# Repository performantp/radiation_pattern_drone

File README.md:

# Radiation Pattern Drone Project 
README

Die mit MMANA oder 4NEC berechneten Antennen sollen mit einer Drohne auf Abstrahlungscharakteristik und Abstrahlungswinkel ausgemessen und überprüft werden. Die erstellten versionierten Dateien sollen für weitere Projektmitglieder lesbar abgelegt werden.

Release 1.3a (diese Aufgabe wurde im September 2021 unterbrochen, weitere Hinweise und Details sind am Schluss aufgeführt).

Release 1.4a es wurden anschliessend zwei Lösungsvarianten evaluiert. 

Variante 1: Welche anfangs Oktober 2021 nun bereits mit einem ersten Test läuft, ist folgende: Mit einem Raspi auf dem rtl_power läuft und RTL-SDR mit einen Transverter
(47g) wird ein Frequenzbereich von 7-14 MHz überwacht und die gemessenen Werte werden mit einem Python Programm auf einem Raspi Zero W (40g) abgegriffen und dargestellt (Kabel und Antennen ca. 50g). Die ersten Messergebnisse sind so, dass man die gemessenen Werte noch gegenüber dem S-Level kalibrieren muss.

Hier ein Test, welcher Signale mit verschiedenen Stärken aufzeigt. Es gibt im Moment jeweils pro Messung ein Bild und eine CSV-Datei. 

Variante 2: Im Hintergrund ist noch folgende zweite Lösung angedacht und die entsprechende Hardware wurde im September 2021 bereits beschafft.
Mit einem Raspi Zero W (40g) sollen die Messwerte von einem RTL-SDR mit integriertem Transverter aufgesammelt werden und die Daten anschliessend mit rtl_power und/oder Python ausgewertet werden.
Es gibt nun ein paar Fotos dazu. Hier ein Rasperi Zero W ohne Gehäuse. 

Das ist ein ganz leichter Rasperi pi-pico mit nur 4g und kann Interpreter-mässig das gleiche wie ein Rasperi Zero W. 

Das ist ein Rasperi Zero W, welcher in einem Gehäude ist und u.U. auch je nach Ausbau noch einen Ventilator hat. 

Der Transverter vor dem RTL. 

Hier sieht man alle Teile vom Transverter, über RTL-SDR und Rasperi im Testaufbau auf dem Balkon von Daniel HB9GVD. Daran angeschlossen ist natürlich noch eine Antenne (nicht sichtbar). 

Wo wir dieses Teil einsetzen hat Martin HB9GYF nach einer Woche vergessen, aber das Bild wird eingetragen und dann nochmals nachgefragt. 

Zu der Programmiersprache Python wurde von HB9FRV Ende September 2021 ein USKA HamAcademy durchgeführt. Es gibt voraussichtlich noch weitere Python Kurse. Auch wie man mit Python SDR Implementationen erstellt, wird von Mathias HB9FRV im Rahmen der USKA HamAcademy vermittelt. Daniel HB9GVD wird am 23.10.2021 am Kurs teilnehmen. Die Kurse sind für USKA Mitglieder mit 60.- CHF Kursgeld zugänglich. Auch dieser Kurs wird ev. wiederholt.

Python ist eine Interpreter Sprache, aber die Source wird auf eine andere Plattform mitgeben. Es wird dann zuerst (einmalig) eine Art Compiler gestartet, der einmal abläuft und dann startet der Interpreter auf diesem Element auf. 

Das Team sucht weitere Interessierte, wenn möglich mit Python Kompetenz, welche die Python Aktivitäten unterstützen können. Interessenten melden sich bitte bei Martin HB9GYF oder Daniel HB9GVD. Martin HB9GYF hat sich Ende Oktober 2021 in der Rolle als Project Manager für den zweiten Python Kurs in der HamAcademy im November 2021 eingetragen, ist aber auf der Warteliste gelandet. Was ist das Ziel? Verstehen, ob ein Project Manager den Python Source Code auf den Ablauf eines Python Programm "lesen" kann. 

Release 1.4b (nächste Aufgabe)
Mit einer grösseren Drohne und einer Last von ca. 150g und einem Gesamtgewicht von mehr als 1kg eine zu messenden Antenne (voraussichtlich eine Small Transmitting Loop (STL)) in einem Stufenflug zu erfliegen, damit daraus die Abstrahlcharakteristik der Antenne ermittelt werden kann. Analysieren wieviele Messungen im Flug pro Sekunde durchgeführt werden müssen, damit die Abstrahlcharakteristik ermittelt werden kann. Analysieren, ob sich im PoC dazu der WSPR-Ansatz eignet. Analysieren, wie z.B. grosse Beam-Antennen auf so kleine Aussendungen in 200m rund um die Antenne reagieren/gemessen werden können. Analysieren, ob sich die kleine Stabantenne im PoC eignet oder ob eine Drahtantenne realisiert werden soll. Analysieren, wie sich eine Aussendung z.B. mit 1W im Flug eignet. Die generelle Datensammlung soll im PoC überprüft werden. Die Datenauswertung im PoC soll nach einem Flug innert 12h vorliegen.

Eine Drohne herzustellen inkl. Akku, GPS und allem SDR-Equipmnet unter 250g wäre interessant, um unter den (künftigen) restriktiven gesetzlichen Anforderungen "in die Luft" zu kommen.

Die Drohne Plan B1 kann mehrere Way Points xyz fliegen und so müssten wir in der Lage sein, unser Stufenprofil auf verschiedenen Höhen auszufliegen. Die Drohne Plan B2 wurde bestellt und ist im September 2021 ebenfalls in der Schweiz bei Daniel HB9GVD. 

Release 1.4c (übernächste Aufgabe)
beinhaltet die Realisierung des sogenannten Datensammelpunkts gemäss Datenmodell sowie der Speicherung der Daten für spätere Auswertungen. Die Empfangssignalstärke sowie die GPS-Daten (es könnten die GPS-Daten der Drohne sein) sollen aufgenommen, zeitlich verknüpft und raw gespeichert werden. 

Release 1.5 (weitere Aufgaben) 
beinhaltet die Realisierung von Auswertungen nach Abzug über WLAN oder Bluetooth von der Drohne auf einen PC. Diese können als erstes Proof of Concept für die Auswertung des Abstrahlwinkels und den weiteren Sendekeulen manuell oder automatisch mit einer Python Programmierung erfolgen. 

---------------------------------------------------------------------------------------------------------------------------------------------------------------------------------
Release 1.3a (diese Aufgabe wurde im September 2021 unterbochen)

Aufgabenstellung: Beinhaltet die Realisierung auf einem eigenen Board mit einem ESP32 Prozessor für die Scriptsprache Phyton mit WLAN und Bluetooth Schnittstelle, welches mit KICAD geplant wird (Design per 15.04.2021 abgeschlossen) und dessen PCB-Fertigung in China inklusive Bestückung erfolgt. Dabei können nur Bauteile vom Produzenten auf der Platine eingebaut werden. Die Integration des Silicon Labs SDR Chipset SI4734-D60-GU (SSOP Bauweise) und weitere 1-2 Bauteile werden dann abschliessend manuell in der Schweiz bestückt und danach getestet. Die Box ohne Antenne ist ca. 5x5x3 cm gross und wird mit ca. 30g Last berechnet. Professionelle Drohne aus US mit 780g Fluggewicht und Funktionen wie u.a. Motion Tracking, Way Point Skills ist nach längeren Shiping Aktionen in der CH eingetroffen und sie wurde getestet. Die vorhandenen Flug Management Skills sind hervorragend, aber u.a. aus Lizenzgründen vermutlich "zu gut". Aus der Sicht maximales Gesamtgewicht, welches unter 250g angestrebt wird (somit ist ein Flug bis 250m Höhe ohne Voranmeldung möglich, gesetzliche Randbedingung) wurde für das PoC eine noch leichtere Drohne bestellt. Die PoC Anforderungen an diese leichte Drohne sind mit Last gesamthaft nicht schwerer als 250g, Way Points zu fliegen, Position halten zu können und alles bis ca. 15 km Wind auf +/- 0.5m genau zu fliegen, und dabei die GPS-Daten zu speichern.  

Das SDR PCB ist am 08.05.2021 fertig "designed" und geht bald in die Fertigung nach China. Screenshot von Daniel HB9GVD erhalten. 

Warum wurde unterbrochen? Beim Testen des Boards sind im August/September 2021 Design-Fehler aufgetreten. Einige Verbindungen konnten zwar mit einer ad hoc Verbindung/Korrektur korrigiert werden. Trotz mehreren Anläufen das Board "zum Laufen" zu bringen, und weiteren Arbeiten wurde der "Durchbruch" leider nicht erreicht. Die Arbeiten zu Release 1.3a wurden deshalb vorläuftig eingestellt, alternative Lösungswege wurden analysiert und gefunden. Gerne lädt das Team Interessierte ein, das Board und die entsprechende Programmierung weiterzuführen. Daniel HB9GVD teilt sein Wissen gerne. Die Gewichtsvorteile der eigenen Hardware würden eher eine <250g Drohne erlauben.

--------------------------------------------------------------------------------------------------------------------------------------------------------------------------------
Abgeschlossene oder gestrichene Releases:
Release 1.1 (am 23.12.2020 abgeschlossen)
beinhaltete die Realisierung im November/Dezember 2020 auf einem Breadboard mit dem Silicon Labs Chipset 30, welcher "nur" MW und FM kann. Die Realiserung mit dem Display ST7735SB mit einer SD-Speicherkarte wurde am 01.12.2020 wegen Inkompatibilität zur Original Display Library eingestellt. Weiter verfolgt wurde die Realisierung mit dem Display ST7735S. Die Realisierung wurde in Woche 50/2020 erfolgreich abgeschlossen. Die erreichten Ergebnisse von diesem Release sind in der Dokumentation festgehalten. 

Release 1.2 (auf diesen Schritt wird am 23.12.2020 verzichtet, weil zwei andere OM's diesen Nachweis bereits vollbracht haben, Verweis auf zwei you tube Videos)
beinhaltet die Realisierung auf einem Breadboard mit dem Silicon Labs SDR Chipset SI4734-D60-GU (in der SSOP Bauweise mit oder ohne Breakout Board), welcher MW, FM und SW, inbesondere LSB, USB und CW, kann. Das Display und die Bedienung wird mit einer App realisiert. 

--------------------------------------------------------------------------------------------------------------------------------------------------------------------------------

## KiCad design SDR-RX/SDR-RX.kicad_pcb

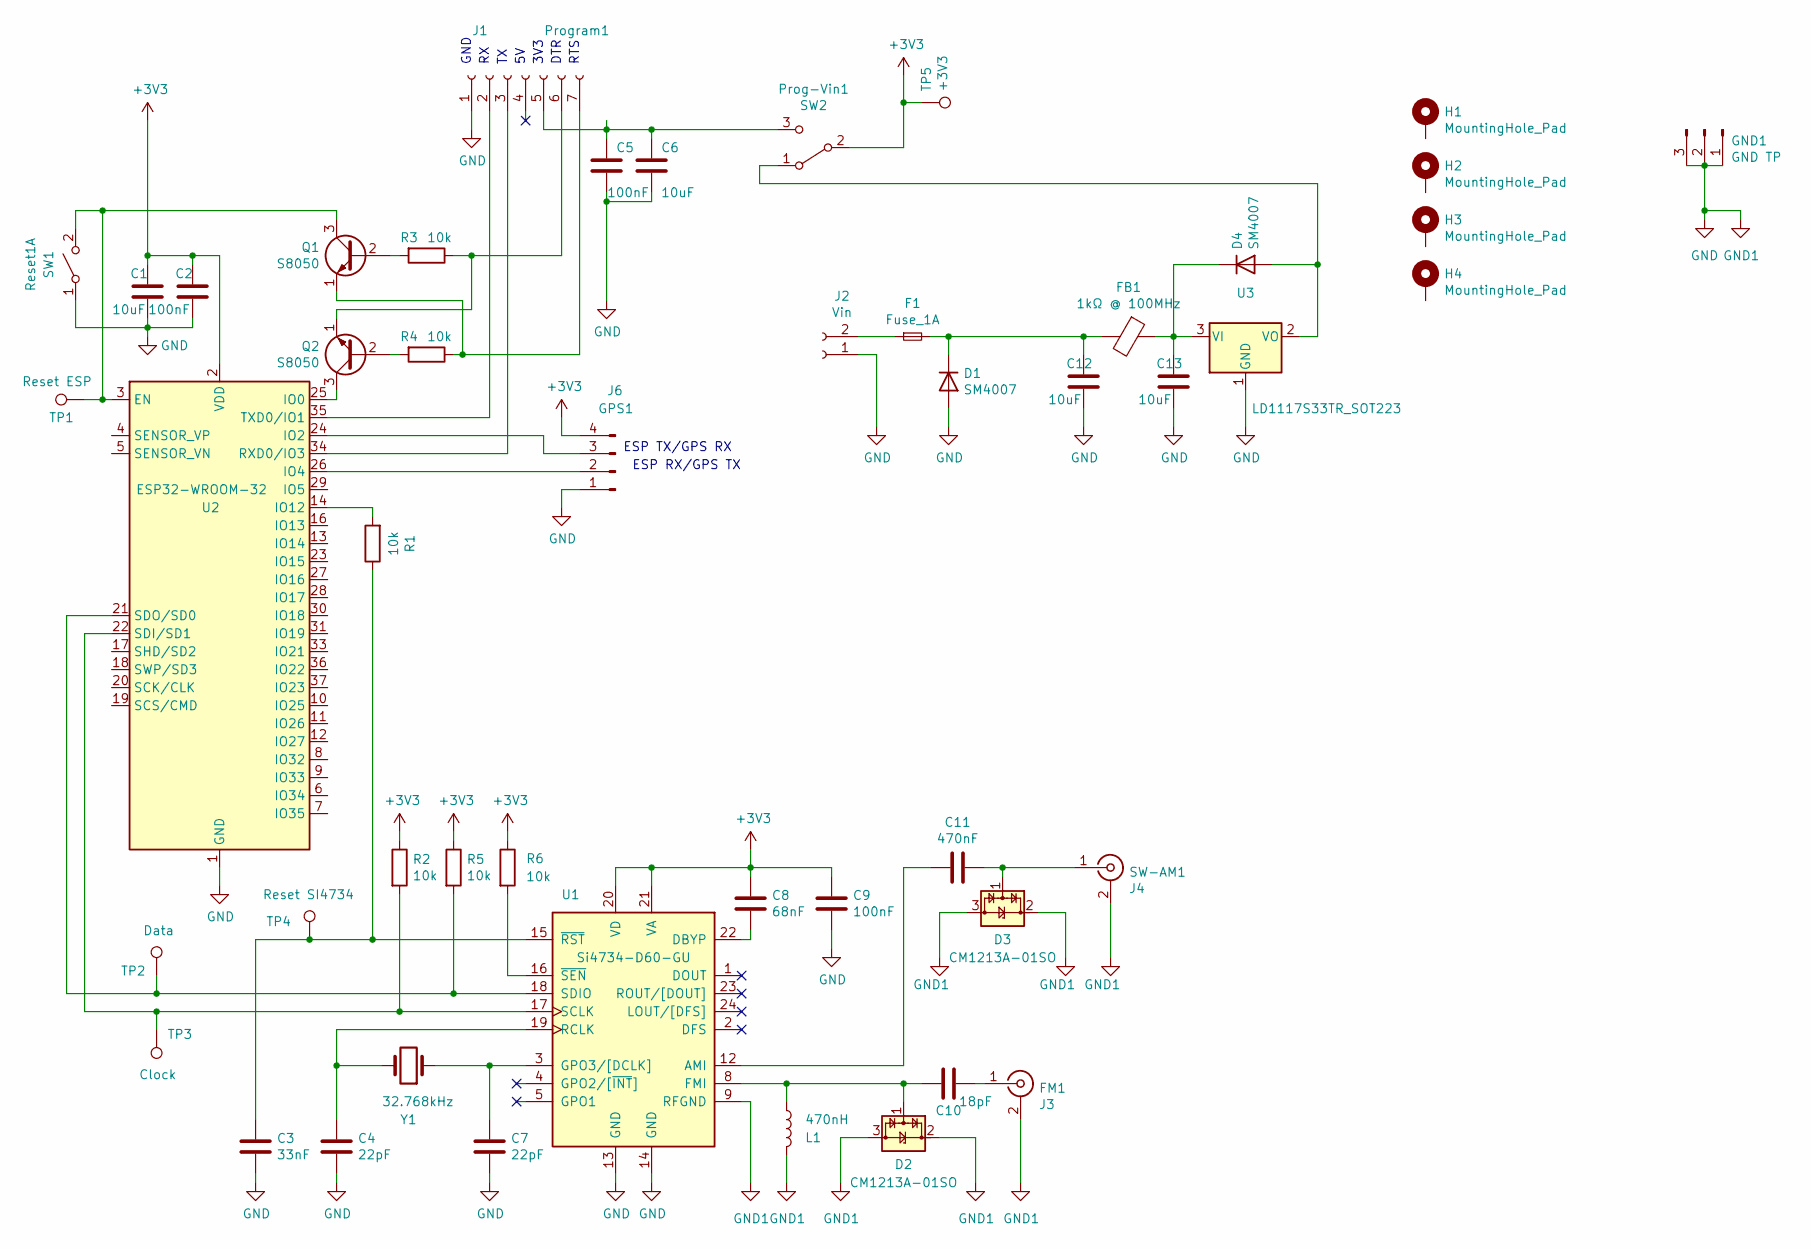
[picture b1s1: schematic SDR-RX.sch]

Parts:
C1, C6, C12, C13: 10uF; C_1206_3216Metric_Pad1.33x1.80mm_HandSolder; LCSC Part # C13585
C2, C5, C9: 100nF; C_0603_1608Metric_Pad1.08x0.95mm_HandSolder; LCSC Part # C14663
C3: 33nF; C_0603_1608Metric_Pad1.08x0.95mm_HandSolder; LCSC Part # C21117
C4, C7: 22pF; C_0603_1608Metric_Pad1.08x0.95mm_HandSolder; LCSC Part # C1653
C8: 68nF; C_0603_1608Metric_Pad1.08x0.95mm_HandSolder; LCSC Part # C31658
C10: 18pF; C_0603_1608Metric_Pad1.08x0.95mm_HandSolder; LCSC Part # C1647
C11: 470nF; C_0603_1608Metric_Pad1.08x0.95mm_HandSolder; LCSC Part # C1623
D1, D4: SM4007; D_1206_3216Metric_Pad1.42x1.75mm_HandSolder; LCSC Part # C64898
D2, D3: CM1213A-01SO; SOT-23
F1: Fuse_1A; Fuse_1206_3216Metric_Pad1.42x1.75mm_HandSolder; LCSC Part # C182308
FB1: 1kΩ @ 100MHz; L_1210_3225Metric_Pad1.42x2.65mm_HandSolder; LCSC Part # C124093
FM1: J3; SMA_Samtec_SMA-J-P-X-ST-EM1_EdgeMount
GND1: GND TP; PinHeader_1x03_P2.54mm_Vertical
GPS1: J6; JST_SH_BM04B-SRSS-TB_1x04-1MP_P1.00mm_Vertical-GPS; LCSC Part # C239522
H1, H2, H3, H4: MountingHole_Pad; MountingHole_2.7mm_Pad_Via
J2: Vin; JST_XH_B2B-XH-A_1x02_P2.50mm_Vertical
L1: 470nH; L_0603_1608Metric_Pad1.05x0.95mm_HandSolder; LCSC Part # C1034
Prog-Vin1: SW2; SW_SPDT_CK-JS102011SAQN; LCSC Part # C160876
Program1: J1; JST_XH_S7B-XH-A-1_1x07_P2.50mm_Horizontal
Q1, Q2: S8050; SOT-23_Handsoldering; LCSC Part # C2146
R1, R2, R3, R4, R5, R6: 10k; R_0603_1608Metric_Pad0.98x0.95mm_HandSolder; LCSC Part # C25804
Reset1: SW1; SW_SPST_B3SL-1002P; LCSC Part # C318887
SW-AM1: J4; SMB_Jack_Vertical
TP1: Reset ESP; TestPoint_Pad_D1.5mm
TP2: Data; TestPoint_Pad_D1.5mm
TP3: Clock; TestPoint_Pad_D1.5mm
TP4: Reset SI4734; TestPoint_Pad_D1.5mm
TP5: +3V3; TestPoint_Pad_D1.5mm
U1: Si4734-D60-GU; SSOP-24_3.9x8.7mm_P0.635mm
U2: ESP32-WROOM-32; LCSC Part # C82899
U3: LD1117S33TR_SOT223; SOT-223-3_TabPin2; LCSC Part # C23984
Y1: 32.768kHz; Crystal_SMD_3215-2Pin_3.2x1.5mm; LCSC Part # C32346

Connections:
+3V3: C1.1, C2.1, C8.1, C9.1, GPS1.4, Prog-Vin1.2 (B), R2.1, R5.1, R6.1, TP5.1, U1.20 (VD), U1.21 (VA), U2.2 (VDD)
GND: C1.2, C2.2, C3.2, C4.1, C5.2, C6.2, C7.2, C9.2, C12.2, C13.2, D1.2 (A), D2.2 (VP), D2.3 (VN), D3.2 (VP), D3.3 (VN), FM1.2 (Ext), GND1.1, GND1.2, GND1.3, GPS1.1, GPS1.MP, J2.1, L1.2, Program1.1, Reset1.1 (A), SW-AM1.2 (Ext), U1.9 (RFGND), U1.13 (GND), U1.14 (GND), U2.1 (GND), U2.15 (GND), U2.38 (GND), U2.39 (GND), U3.1 (GND)
unnamed: C3.1, R1.1, TP4.1, U1.15 (~RST)
unnamed: C4.2, U1.19 (RCLK), Y1.2
unnamed: C5.1, C6.1, Prog-Vin1.3 (C), Program1.5
unnamed: C7.1, U1.3 (GPO3/[DCLK]), Y1.1
unnamed: C8.2, U1.22 (DBYP)
unnamed: C10.1, FM1.1 (In)
unnamed: C10.2, D2.1 (CH1), L1.1, U1.8 (FMI)
unnamed: C11.1, D3.1 (CH1), SW-AM1.1 (In)
unnamed: C11.2, U1.12 (AMI)
unnamed: C12.1, D1.1 (K), F1.2, FB1.2
unnamed: C13.1, D4.1 (K), FB1.1, U3.3 (VI)
unnamed: D4.2 (A), Prog-Vin1.1 (A), U3.2 (VO)
unnamed: F1.1, J2.2
unnamed: GPS1.2, U2.26 (IO4)
unnamed: GPS1.3, U2.24 (IO2)
unnamed: Program1.2, U2.35 (TXD0/IO1)
unnamed: Program1.3, U2.34 (RXD0/IO3)
unnamed: Program1.6, Q2.1 (E), R3.1
unnamed: Program1.7, Q1.1 (E), R4.1
unnamed: Q1.2 (B), R3.2
unnamed: Q1.3 (C), Reset1.2 (B), TP1.1, U2.3 (EN)
unnamed: Q2.2 (B), R4.2
unnamed: Q2.3 (C), U2.25 (IO0)
unnamed: R1.2, U2.14 (IO12)
unnamed: R2.2, TP3.1, U1.17 (SCLK), U2.22 (SDI/SD1)
unnamed: R5.2, TP2.1, U1.18 (SDIO), U2.21 (SDO/SD0)
unnamed: R6.2, U1.16 (~SEN)

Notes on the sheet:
3V3
DTR
RTS
GND
ESP RX/GPS TX
ESP TX/GPS RX

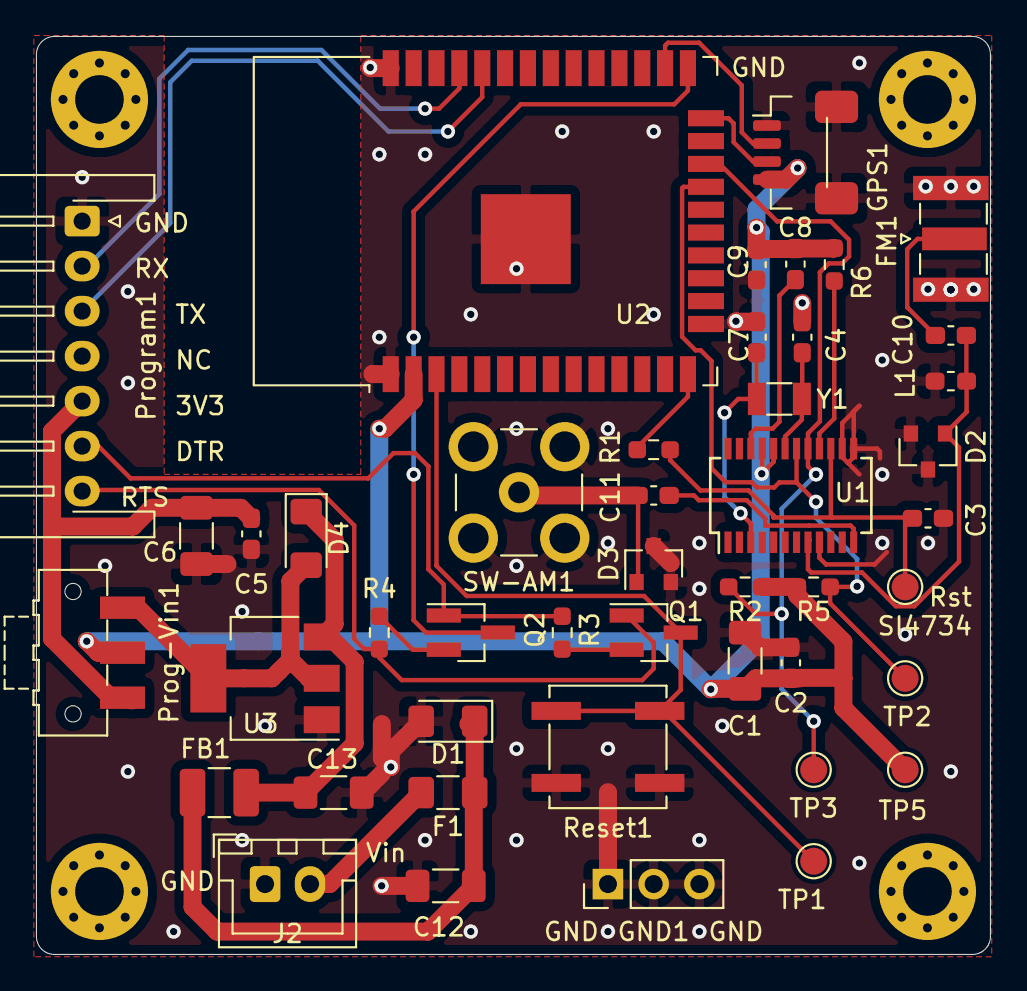
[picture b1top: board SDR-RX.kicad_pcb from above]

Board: 2 copper layers, 53.0 x 51.0 mm, 49 parts (0 on the bottom side), 29 nets.

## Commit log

2020-12-02 Create README.md
    Release Planung am 02.12.2020 erstellt.
    Im Moment arbeiten wir für den Release 1.1 im Main und wir werden am Schluss den Release schliessen, wenn die Arbeiten für Release 1.2 beginnen.
2020-12-02 Update README.md
    Typos korrigiert.
2020-12-02 Update README.md
    Noch zwei Typos gefunden und korrigiert.
2020-12-02 Add files via upload
    Diese vier Dateien sind von Martin mit dem Stand vom 01.12.2020. Es gibt in der Zwischenzeit betreits schon neuere Arbeitsdokumente, und auch dieser Update wird so dann noch ausgetestet.
2020-12-02 Add files via upload
    Dies ist die Spezifikation vom Hersteller Silicon Labs über die leicht neuere SDR Chipreihe mit zwei unterschiedlichen Bauformen. Dabei ist darauf zu achten, dass wir erstens jeweils die Funktion SW 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
2020-12-02 Add files via upload
    Der Hersteller Silicon Labs gibt Unterlagen und Spezifikationen für die Antenne bekannt, welche berücksichtigt werden müssen.
2020-12-02 Add files via upload
    Die ist ein Schema, welches das Projekt von Xhackster verwendet. In diesem Fall wird der Chipset SI4630-D60 in der quadratischen Form verwendet, welcher aber bereits SW kann. Diesen Chip haben wir fü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
2020-12-02 Add files via upload
    Dies ist der Original Code aus dem Xhackster Projekt, welches mit dem SI4730-D60 Chip (mit SW) arbeitet. Wir haben diesen Code mit den entsprechenden Libraries ausprobiert, aber am 03.12.2020 noch ni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
2020-12-03 Update README.md
    Mit dem Release 1.2a "Empfangssignalstärke verknüpft mit den GPS-Daten am Datensammlungspunkt " werden wir überprüfen können, wie der Empfang an einer Live-Antenne im Feld aufgenommen werden können.
2020-12-04 Changed main title in README file
2020-12-04 Originalcode von CesarSound (hackster.io)
    Dieser Commit enthält den von CesarSound auf hackster.io publizierten Originalcode zur Ansteuerung des si4730/35 Chips inkl. TFT Display. Sein Schema sowie die notwendigen Arduino-Library Abhängigkei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
2020-12-04 Source Code und Schema von CesarSound aus Wurzelverzeichnis gelöscht
    Diese DAten sind neu im RX_SI4735_30_TFT_ST7735_SHARE_JCR_REV_2_1 Unterverzeichnis zu finden.
2020-12-04 Verschiebe si4730 Datenblatt ins *datasheets" Unterverzeichnis.
2020-12-05 Update README.md
    Die Bezeichnung SI4734-D60-GU an zwei Stellen korrigiert.
2020-12-06 Update README.md
    SI4734-D60-GU korrekt eingetragen
2020-12-06 Delete Anforderungskatalog Mit einer Drohne eine Antenne ausmessen.docx
    Martin löscht diese Datei, weil ich sie in dem Ordner Docs und nicht flat haben will. Aber mit GitHub Desktop habe ich das 'rename' wie es Mathias in Tortoise gezeigt hat, nicht verstanden.
2020-12-06 Delete Anforderungskatalog Mit einer Drohne eine Antenne ausmessen.html
    Martin löscht diese Datei, weil ich sie in dem Ordner Docs und nicht flat haben will. Aber mit GitHub Desktop habe ich das 'rename' wie es Mathias in Tortoise gezeigt hat, nicht verstanden.
2020-12-06 Delete Anforderungskatalog Mit einer Drohne eine Antenne ausmessen.mmap
    Martin löscht diese Datei, weil ich sie in dem Ordner Docs und nicht flat haben will. Aber mit GitHub Desktop habe ich das 'rename' wie es Mathias in Tortoise gezeigt hat, nicht verstanden.
2020-12-06 Delete Anforderungskatalog Mit einer Drohne eine Antenne ausmessen.pdf
    Martin löscht diese Datei, weil ich sie in dem Ordner Docs und nicht flat haben will. Aber mit GitHub Desktop habe ich das 'rename' wie es Mathias in Tortoise gezeigt hat, nicht verstanden.
2020-12-06 Create xxx
    Den Folder Docs erstellt, damit ich meine Dokumentationen dort hinauf laden kann.
2020-12-06 Add files via upload
    Martin hat die vier Dateien zweimal hochgeladen. Ich habe noch nicht herausgefunden wo die ersten vier hingeschickt wurden. Nun sollten diese vier im Ordner Docs sein. Hoffentlich.
2020-12-06 Delete xxx
    Wenn man einen neuen Ordner erstellt und hier war es der Ordner Docs, musste ich einen Dateinamen angeben. Deshalb wird nun die Datei xxx gelöscht. So ist es nun bereinigt. Aber ich weiss immer noch 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
2020-12-07 Add files via upload
    Die Dokumentation mit dem Stand vom 05.12.2020 wird am 07.12.2020 hochgeladen.
2020-12-19 Die Dokumentation von Martin bis und mit 19.12.2020 wird hochgeladen
    Die Datei sind aus dem lokalen Directory von Martin, sprich ein normales Filesystem (kein export mit Tortoise aus dem GitHub). Das Word File konnte per 19.12.2020 nicht aus dem Mind Map exportiert we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
2020-12-19 Word Datei als Export von Mind Map
    Martin musste Verbindungen im Mind Map löschen, damit der Export ins Word klappte. Dies ist die Dokumentation per 19.12.2020
2020-12-19 Dies ist nun das Word File der Dokumentation per 19.12.2020
    Es mussten Verbindungen im Mind Map gelöscht werden, damit der Export ins Word klappt.
2020-12-21 erste Schema Version für das SDR-RX-PCB
2020-12-23 Update README.md
    Anpassungen der Release Planung aus der Sicht vom 23.12.2020
2020-12-23 Update README.md
    Typos
2020-12-23 Präzisierung einer Anforderung
    Die Anzeige und Bedienung erfolgt über eine App
2021-01-10 Antennenteil bis SMA Stecker im Schema hinzugefügt
2021-01-14 Added pullups/down to GPO1, GPO2 of RF and EN of ESP
2021-01-31 Added Peripheral Schematics for ESP32-WROOM-32-D 3V3 regulator still missing
2021-02-21 Added power supply path
2021-03-24 Changes at ESP Reset, Data/Clock wired, Antenna changes
2021-03-26 added datasheets
2021-03-26 Project & PCB file added
2021-03-26 changed J2 footprint
2021-03-26 added SW2
2021-03-26 rearanged parts
2021-03-27 put parts closer on PCB
2021-03-27 rearraanged RF parts
2021-04-09 PCB layout for plastic enclosure
2021-04-15 Update README.md
    Das Readme wurde nach der Besprechung mit Dani HB9GVD Mitte April 2021 durch Martin HB9GYF angepasst.
2021-04-16 Das Datenmodell noch vom Dezember 2020
    Muss noch erweitert werden, aber besser als nichts.
2021-04-16 Datenmodell aus Dezember 2020
    Muss noch ergänzt werden, aber besser als nichts. Hier noch das .vsd File.
2021-04-16 Mindmap Mitte April 2021
    Mindmap Mitte mit Stand Mitte April 2021 wird hochgeladen
2021-04-16 Word Mitte April 2021
    Word mit Stand Mitte April 2021 wird hochgeladen
2021-04-16 PDF Mitte April 2021
    PDF mit Stand Mitte April 2021 wird hochgeladen
2021-04-16 HTML Mitte April 2021
    HTML mit Stand Mitte April 2021 wird hochgeladen
2021-04-16 Readme.english.md
    Why the the suffix is inly "md" shall be taken under investigation.
2021-04-16 Typos
    Typos
2021-04-16 README in capitol letters
    README in capitol letters
2021-04-16 Update README.english.md
    Capital letters.
2021-04-16 Update README.english.md
    First draft without translation service.
2021-04-16 Update README.english.md
    Typos corrected.
2021-04-27 changed footprint GPS header
2021-05-03 round corners
2021-05-05 routed without GND
2021-05-05 closed misssing copper
2021-05-06 PCB routed
2021-05-08 sticked back and front GND zones with vias
2021-05-08 SDR PCB ist fertig
    Den Screenshot von Daniel HB9GVD einfügen.
2021-05-08 SDR PCB
    Mit dem Snipping Tool habe ich einfach einen Shot von der -png Datei gezogen und eingefügt.
2021-05-08 Drohne Plan B1
    Drohne Plan B1 liegt vor und die Drohne Plan B2 wurde bestellt.
2021-05-08 Update
    Typos
2021-05-08 SDR PCB
    SDR PCR has been designed and reviewed and it reada to be produced in the factory in China.
2021-05-22 removed obsolete GND vias
2021-05-25 Added BOM and schematics.pdf
2021-05-26 Minimize overlap of traces with ESP "keep out" zone for antenna
2021-05-26 Optimizing position of various silk screen elements
2021-05-26 Registering local hb9uf.pretty repo as project submodule
2021-05-26 Adding hb9uf.pretty to local footprint library (fp-lib-table)
2021-05-26 Adding HB9UF logo to PCB (to be positioned)
2021-06-01 Added silk-screen text and logo
2021-06-01 V1 submission files generated, some troubles with rotation of CPL detected
2021-06-02 some local files deleted to regain last SDR-RX.kicad_pcb merged monday with frv branch
2021-06-02 added teyt as Title and Copyright
2021-06-02 added OSHW logo
2021-06-02 minor changes on silkscreen Program connector and removed strange GND symbol
2021-06-02 created production files, unfortunatelly there is a missrotation on parts
2021-06-02 added drillfiles
2021-06-02 fixed reversed comment/designator for switches and connectors to be pick and placed. TODO: need to be changed as well in schema/pcb files
2021-06-03 changed footprint D1 & D4 due to assembly objection
2021-06-03 moved Prog-Vin1 switch closer to pcb edge, changed anotation GND1 of GND TP
2021-06-03 changed Designator J5 to Program1 to avoid BPM/CPL missmatch on SMT assembly
2021-06-03 reversed remaining value/designator of all connectors
2021-06-03 adapted footprint of GPS1/J6 to real footprint of SMT assembly, created hb9gvd.pretty directory
2021-06-03 created production files
2021-06-03 added gerber and hb9gvd.pretty
2021-10-11 Update README.md
    Readme nach der Besprechung mit Daniel GB9GVD am 11.10.2021 nachgeführt.
2021-10-11 Update README.english.md
    Update as of October 11, 2021.
2021-10-11 Update README.english.md
    Typos
2021-10-12 Update README.md
    Daniel HB9GVD hat seine Korrekturen zum Readme Deutsch geliefert und Martin HB9GYF hat sie nun nachgetragen
2021-10-12 Revert "Develop docs martin"
2022-01-26 Initial commit of power_detector.py
2022-02-03 Sum bin magnitudes instead of extracting max. magnitude (peak value)
    This is a better approach in particular if our signal is not an
    unmodulated carrier.
2022-04-17 Added gps time, coordinate, high above see level
2022-04-17 wrong filename
2022-04-17 Added GPS output via gpscsv/gpsd
2022-06-05 example to read nmea stream from serial connection

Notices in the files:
SDR-RX/SDR-RX.kicad_pcb:
(c) 2012 Daniel HB9GVD CC-BY-SA
